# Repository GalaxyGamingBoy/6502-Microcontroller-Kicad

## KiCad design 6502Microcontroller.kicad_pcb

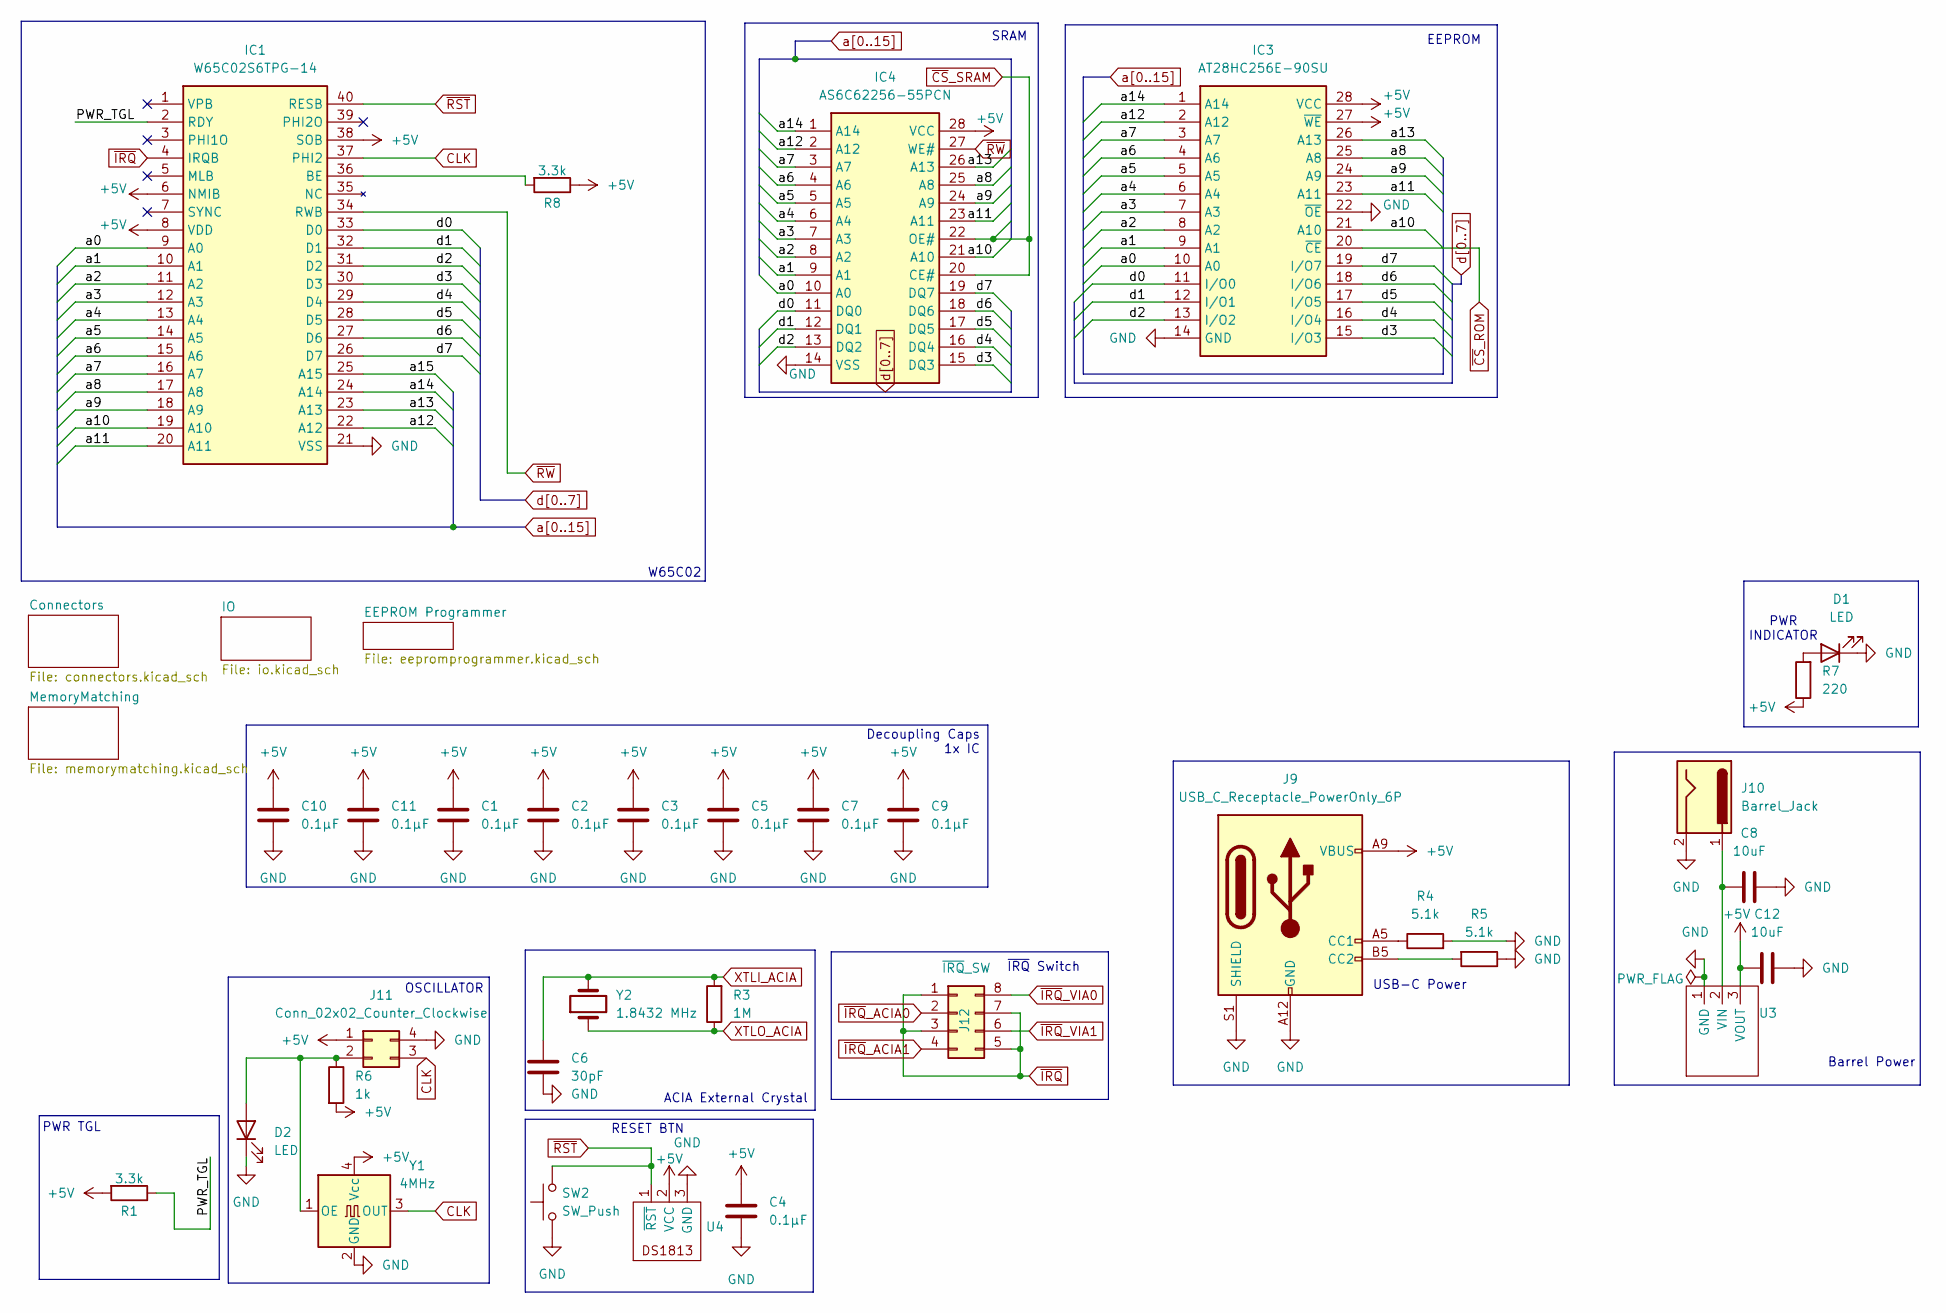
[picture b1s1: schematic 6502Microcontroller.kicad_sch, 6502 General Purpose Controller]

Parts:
C1, C2, C3, C4, C5, C7, C9, C10, C11: 0.1µF; C_0603_1608Metric_Pad1.08x0.95mm_HandSolder
C6: 30pF; C_0603_1608Metric_Pad1.08x0.95mm_HandSolder
C8, C12: 10uF; C_0603_1608Metric_Pad1.08x0.95mm_HandSolder
D1, D2: LED; LED_0603_1608Metric_Pad1.05x0.95mm_HandSolder
IC1: W65C02S6TPG-14; DIP-40_L50.8-W17.8-P2.54-LS15.2-BL; Mouser Part Number 955-W65C02S6TPG-14
IC3: AT28HC256E-90SU; DIP-28_L35.6-W10.2-P2.54-LS7.6-BL-A; Mouser Part Number 556-AT28HC256E90SU
IC4: AS6C62256-55PCN; DIP-28_L35.6-W10.2-P2.54-LS7.6-BL-A; Mouser Part Number 913-AS6C62256-55PCN
J9: USB_C_Receptacle_PowerOnly_6P; USB-C-SMD
J10: Barrel_Jack; BarrelJack_Horizontal
J11: Conn_02x02_Counter_Clockwise; HDR-TH_4P-P2.54-V-F-R2-C2-S2.54
J12: ~{IRQ}_SW; HDR-TH_8P-P2.54-V-M-R2-C4-S2.54
R1, R8: 3.3k; R_0603_1608Metric_Pad0.98x0.95mm_HandSolder
R3: 1M; R_0603_1608Metric_Pad0.98x0.95mm_HandSolder
R4, R5: 5.1k; R_0603_1608Metric_Pad0.98x0.95mm_HandSolder
R6: 1k; R_0603_1608Metric_Pad0.98x0.95mm_HandSolder
R7: 220; R_0603_1608Metric_Pad0.98x0.95mm_HandSolder
SW2: SW_Push; SW-SMD_L3.9-W3.0-P4.45
U3: SOT-89-3_L4.5-W2.5-P1.50-LS4.2-BR
U4: SOT-23-3_L2.9-W1.3-P1.90-LS2.4-BR
Y1: 4MHz; OSC-SMD_4P-L7.0-W5.0-BL-2
Y2: 1.8432 MHz; MP018B

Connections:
+5V: C1.1, C2.1, C3.1, C4.2, C5.1, C7.1, C9.1, C10.1, C11.1, C12.2, IC1.6 (NMIB), IC1.8 (VDD), IC1.38 (SOB), IC3.27 (~WE), IC3.28 (VCC), IC4.28 (VCC), J9.A9 (VBUS), J9.B9 (VBUS), J11.1, R1.2, R6.2, R7.1, R8.1, U3.3 (VOUT), U4.2 (VCC), Y1.4 (Vcc); also elsewhere on the board
/PWR_TGL: IC1.2 (RDY), R1.1
CLK: IC1.37 (PHI2), J11.3, Y1.3 (OUT); also elsewhere on the board
GND: C1.2, C2.2, C3.2, C4.1, C5.2, C6.2, C7.2, C8.2, C9.2, C10.2, C11.2, C12.1, D1.1 (K), D2.1 (K), IC1.21 (VSS), IC3.14 (GND), IC3.22 (~OE), IC4.14 (VSS), J9.A12 (GND), J9.B12 (GND), J9.S1 (SHIELD), J10.2, J11.4, R4.2, R5.1, SW2.1, U3.1 (GND), U4.3 (GND), Y1.2 (GND); also elsewhere on the board
unnamed: D1.2 (A), R7.2
unnamed: D2.2 (A), J11.2, R6.1, Y1.1 (OE)
unnamed: IC1.36 (BE), R8.2
unnamed: J9.A5 (CC1), R4.1
unnamed: J9.B5 (CC2), R5.2
unnamed: C8.1, J10.1, U3.2 (VIN)
XTLI_ACIA: C6.1, R3.2, Y2.2; also elsewhere on the board
XTLO_ACIA: R3.1, Y2.1; also elsewhere on the board
a0: IC1.9 (A0), IC3.10 (A0), IC4.10 (A0); also elsewhere on the board
a1: IC1.10 (A1), IC3.9 (A1), IC4.9 (A1); also elsewhere on the board
a2: IC1.11 (A2), IC3.8 (A2), IC4.8 (A2); also elsewhere on the board
a3: IC1.12 (A3), IC3.7 (A3), IC4.7 (A3); also elsewhere on the board
a4: IC1.13 (A4), IC3.6 (A4), IC4.6 (A4)
a5: IC1.14 (A5), IC3.5 (A5), IC4.5 (A5)
a6: IC1.15 (A6), IC3.4 (A6), IC4.4 (A6)
a7: IC1.16 (A7), IC3.3 (A7), IC4.3 (A7)
a8: IC1.17 (A8), IC3.25 (A8), IC4.25 (A8)
a9: IC1.18 (A9), IC3.24 (A9), IC4.24 (A9)
a10: IC1.19 (A10), IC3.21 (A10), IC4.21 (A10); also elsewhere on the board
a11: IC1.20 (A11), IC3.23 (A11), IC4.23 (A11); also elsewhere on the board
a12: IC1.22 (A12), IC3.2 (A12), IC4.2 (A12); also elsewhere on the board
a13: IC1.23 (A13), IC3.26 (A13), IC4.26 (A13); also elsewhere on the board
a14: IC1.24 (A14), IC3.1 (A14), IC4.1 (A14); also elsewhere on the board
a15: IC1.25 (A15); also elsewhere on the board
d0: IC1.33 (D0), IC3.11 (I/O0), IC4.11 (DQ0); also elsewhere on the board
d1: IC1.32 (D1), IC3.12 (I/O1), IC4.12 (DQ1); also elsewhere on the board
d2: IC1.31 (D2), IC3.13 (I/O2), IC4.13 (DQ2); also elsewhere on the board
d3: IC1.30 (D3), IC3.15 (I/O3), IC4.15 (DQ3); also elsewhere on the board
d4: IC1.29 (D4), IC3.16 (I/O4), IC4.16 (DQ4); also elsewhere on the board
d5: IC1.28 (D5), IC3.17 (I/O5), IC4.17 (DQ5); also elsewhere on the board
d6: IC1.27 (D6), IC3.18 (I/O6), IC4.18 (DQ6); also elsewhere on the board
d7: IC1.26 (D7), IC3.19 (I/O7), IC4.19 (DQ7); also elsewhere on the board
~CS_ROM: IC3.20 (~CE); also elsewhere on the board
~CS_SRAM: IC4.20 (CE#), IC4.22 (OE#); also elsewhere on the board
~IRQ: IC1.4 (IRQB), J12.1, J12.3, J12.5, J12.7
~IRQ_ACIA0: J12.2; also elsewhere on the board
~IRQ_ACIA1: J12.4; also elsewhere on the board
~IRQ_VIA0: J12.8; also elsewhere on the board
~IRQ_VIA1: J12.6; also elsewhere on the board
~RST: IC1.40 (RESB), SW2.2, U4.1 (~RST); also elsewhere on the board
~RW: IC1.34 (RWB), IC4.27 (WE#); also elsewhere on the board

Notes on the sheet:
PWR TGL
EEPROM
RESET BTN
~{IRQ} Switch
PWR INDICATOR
OSCILLATOR
Decoupling Caps 1x IC
ACIA External Crystal
SRAM
W65C02
Barrel Power
USB-C Power

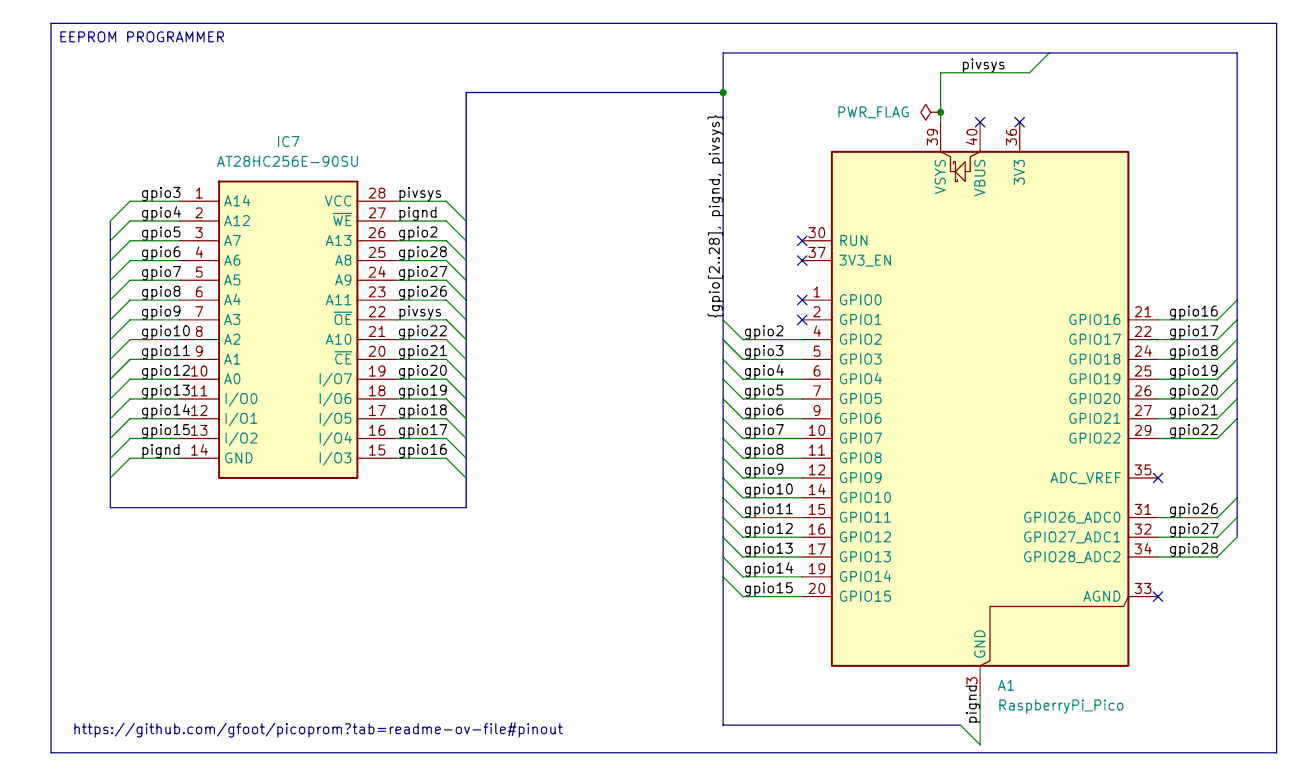
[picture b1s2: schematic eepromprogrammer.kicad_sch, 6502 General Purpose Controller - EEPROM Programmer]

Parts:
A1: RaspberryPi_Pico
IC7: AT28HC256E-90SU; Mouser Part Number 556-AT28HC256E90SU

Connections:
unnamed: A1.4 (GPIO2), IC7.26 (A13)
unnamed: A1.5 (GPIO3), IC7.1 (A14)
unnamed: A1.6 (GPIO4), IC7.2 (A12)
unnamed: A1.7 (GPIO5), IC7.3 (A7)
unnamed: A1.9 (GPIO6), IC7.4 (A6)
unnamed: A1.10 (GPIO7), IC7.5 (A5)
unnamed: A1.11 (GPIO8), IC7.6 (A4)
unnamed: A1.12 (GPIO9), IC7.7 (A3)
unnamed: A1.3 (GND), A1.8 (GND), A1.13 (GND), A1.18 (GND), A1.23 (GND), A1.28 (GND), A1.38 (GND), IC7.14 (GND), IC7.27 (~WE)
unnamed: A1.14 (GPIO10), IC7.8 (A2)
unnamed: A1.15 (GPIO11), IC7.9 (A1)
unnamed: A1.16 (GPIO12), IC7.10 (A0)
unnamed: A1.17 (GPIO13), IC7.11 (I/O0)
unnamed: A1.19 (GPIO14), IC7.12 (I/O1)
unnamed: A1.20 (GPIO15), IC7.13 (I/O2)
unnamed: A1.21 (GPIO16), IC7.15 (I/O3)
unnamed: A1.22 (GPIO17), IC7.16 (I/O4)
unnamed: A1.24 (GPIO18), IC7.17 (I/O5)
unnamed: A1.25 (GPIO19), IC7.18 (I/O6)
unnamed: A1.26 (GPIO20), IC7.19 (I/O7)
unnamed: A1.27 (GPIO21), IC7.20 (~CE)
unnamed: A1.29 (GPIO22), IC7.21 (A10)
unnamed: A1.31 (GPIO26_ADC0), IC7.23 (A11)
unnamed: A1.32 (GPIO27_ADC1), IC7.24 (A9)
unnamed: A1.34 (GPIO28_ADC2), IC7.25 (A8)
unnamed: A1.39 (VSYS), IC7.22 (~OE), IC7.28 (VCC)

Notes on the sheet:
EEPROM PROGRAMMER
https://github.com/gfoot/picoprom?tab=readme-ov-file#pinout

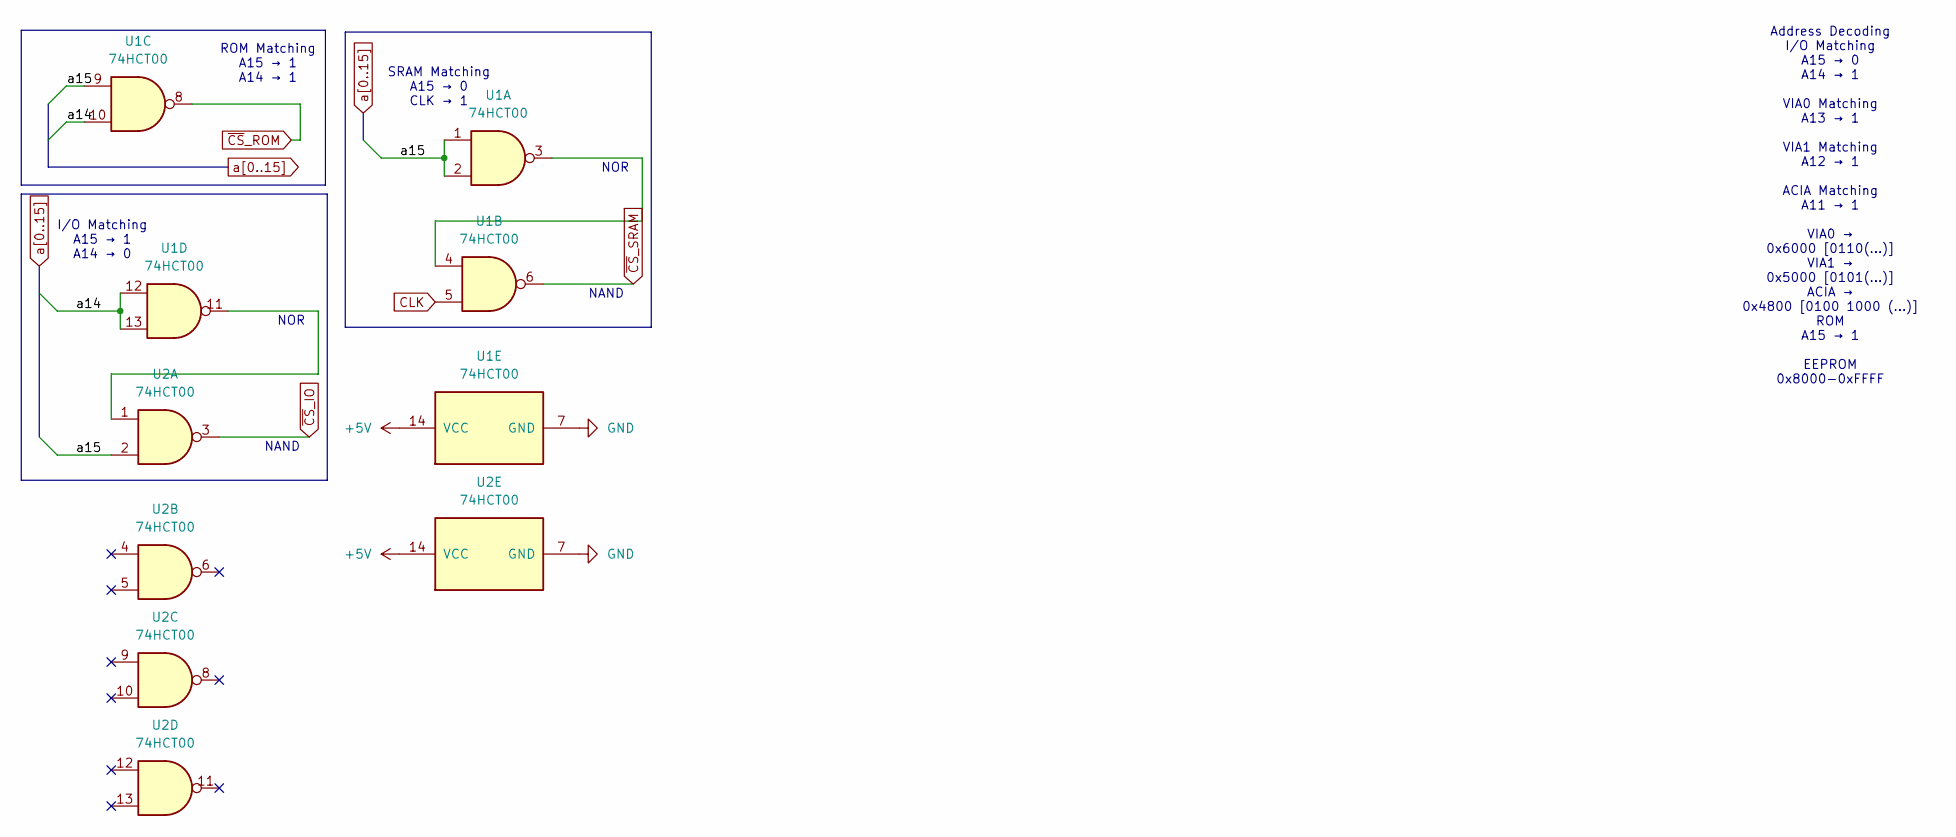
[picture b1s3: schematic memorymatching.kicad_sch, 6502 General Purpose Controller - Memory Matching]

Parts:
U1, U2: 74HCT00; DIP-14_L17.8-W10.2-P2.54-BL

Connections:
+5V: U1.14 (VCC), U2.14 (VCC); also elsewhere on the board
CLK: U1.5; also elsewhere on the board
GND: U1.7 (GND), U2.7 (GND); also elsewhere on the board
unnamed: U1.3, U1.4
unnamed: U1.11, U2.1
a14: U1.10, U1.12, U1.13; also elsewhere on the board
a15: U1.1, U1.2, U1.9, U2.2; also elsewhere on the board
~CS_IO: U2.3; also elsewhere on the board
~CS_ROM: U1.8; also elsewhere on the board
~CS_SRAM: U1.6; also elsewhere on the board

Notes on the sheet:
NOR
Address Decoding I/O Matching A15 → 0 A14 → 1 VIA0 Matching A13 → 1 VIA1 Matching A12 → 1 ACIA Matching A11 → 1 VIA0 → 0x6000 [0110(...)] VIA1 → 0x5000 [0101(...)] ACIA → 0x4800 [0100 1000 (...)] ROM A15 → 1 EEPROM 0x8000-0xFFFF
I/O Matching A15 → 1 A14 → 0
SRAM Matching A15 → 0 CLK → 1
NAND
ROM Matching A15 → 1 A14 → 1

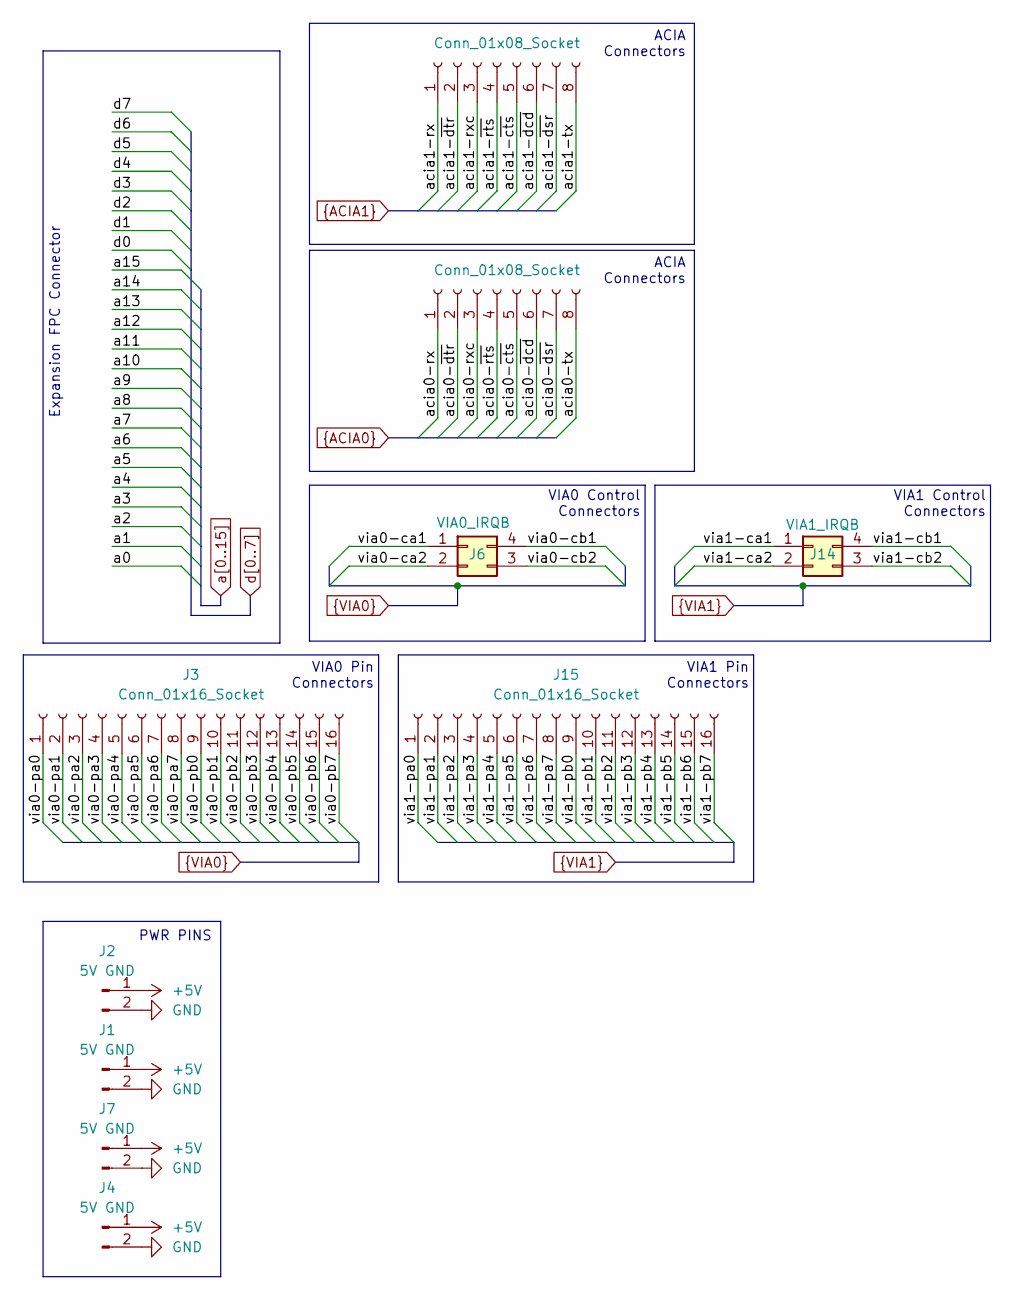
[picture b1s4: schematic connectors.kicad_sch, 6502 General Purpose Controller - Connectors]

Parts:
J1, J2, J4, J7: 5V GND; HDR-TH_2P-P2.54-V-F-1
J3, J15: Conn_01x16_Socket; HDR-TH_16P-P2.54-V-F-4
J5, J8: Conn_01x08_Socket; HDR-TH_8P-P2.54-V-F
J6: VIA0_IRQB; HDR-TH_4P-P2.54-V-F-R2-C2-S2.54
J14: VIA1_IRQB; HDR-TH_4P-P2.54-V-F-R2-C2-S2.54

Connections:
+5V: J1.1, J2.1, J4.1, J7.1; also elsewhere on the board
GND: J1.2, J2.2, J4.2, J7.2; also elsewhere on the board
acia0-rx: J5.1; also elsewhere on the board
acia0-rxc: J5.3; also elsewhere on the board
acia0-tx: J5.8; also elsewhere on the board
acia0-~cts: J5.5; also elsewhere on the board
acia0-~dcd: J5.6; also elsewhere on the board
acia0-~dsr: J5.7; also elsewhere on the board
acia0-~dtr: J5.2; also elsewhere on the board
acia0-~rts: J5.4; also elsewhere on the board
acia1-rx: J8.1; also elsewhere on the board
acia1-rxc: J8.3; also elsewhere on the board
acia1-tx: J8.8; also elsewhere on the board
acia1-~cts: J8.5; also elsewhere on the board
acia1-~dcd: J8.6; also elsewhere on the board
acia1-~dsr: J8.7; also elsewhere on the board
acia1-~dtr: J8.2; also elsewhere on the board
acia1-~rts: J8.4; also elsewhere on the board
via0-ca1: J6.1; also elsewhere on the board
via0-ca2: J6.2; also elsewhere on the board
via0-cb1: J6.4; also elsewhere on the board
via0-cb2: J6.3; also elsewhere on the board
via0-pa0: J3.1; also elsewhere on the board
via0-pa1: J3.2; also elsewhere on the board
via0-pa2: J3.3; also elsewhere on the board
via0-pa3: J3.4; also elsewhere on the board
via0-pa4: J3.5; also elsewhere on the board
via0-pa5: J3.6; also elsewhere on the board
via0-pa6: J3.7; also elsewhere on the board
via0-pa7: J3.8; also elsewhere on the board
via0-pb0: J3.9; also elsewhere on the board
via0-pb1: J3.10; also elsewhere on the board
via0-pb2: J3.11; also elsewhere on the board
via0-pb3: J3.12; also elsewhere on the board
via0-pb4: J3.13; also elsewhere on the board
via0-pb5: J3.14; also elsewhere on the board
via0-pb6: J3.15; also elsewhere on the board
via0-pb7: J3.16; also elsewhere on the board
via1-ca1: J14.1; also elsewhere on the board
via1-ca2: J14.2; also elsewhere on the board
via1-cb1: J14.4; also elsewhere on the board
via1-cb2: J14.3; also elsewhere on the board
via1-pa0: J15.1; also elsewhere on the board
via1-pa1: J15.2; also elsewhere on the board
via1-pa2: J15.3; also elsewhere on the board
via1-pa3: J15.4; also elsewhere on the board
via1-pa4: J15.5; also elsewhere on the board
via1-pa5: J15.6; also elsewhere on the board
via1-pa6: J15.7; also elsewhere on the board
via1-pa7: J15.8; also elsewhere on the board
via1-pb0: J15.9; also elsewhere on the board
via1-pb1: J15.10; also elsewhere on the board
via1-pb2: J15.11; also elsewhere on the board
via1-pb3: J15.12; also elsewhere on the board
via1-pb4: J15.13; also elsewhere on the board
via1-pb5: J15.14; also elsewhere on the board
via1-pb6: J15.15; also elsewhere on the board
via1-pb7: J15.16; also elsewhere on the board

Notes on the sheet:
ACIA Connectors
Expansion FPC Connector
VIA0 Control Connectors
PWR PINS
VIA1 Pin Connectors
VIA1 Control Connectors
VIA0 Pin Connectors

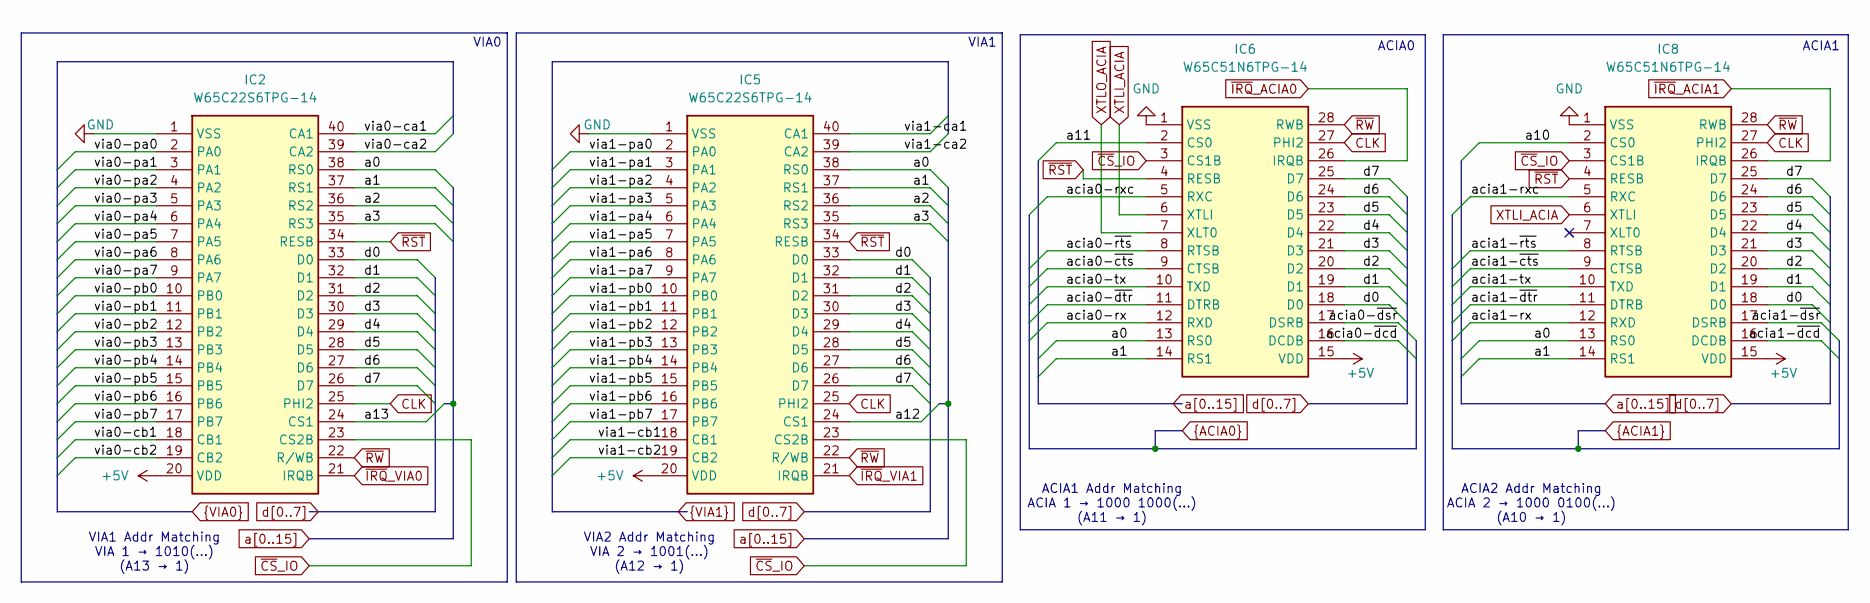
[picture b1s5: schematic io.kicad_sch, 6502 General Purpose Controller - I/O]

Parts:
IC2, IC5: W65C22S6TPG-14; DIP-40_L50.8-W17.8-P2.54-LS15.2-BL; Mouser Part Number 955-W65C22S6TPG-14
IC6, IC8: W65C51N6TPG-14; DIP-28_L35.6-W10.2-P2.54-LS7.6-BL-A; Mouser Part Number 955-W65C51N6TPG-14

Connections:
+5V: IC2.20 (VDD), IC5.20 (VDD), IC6.15 (VDD), IC8.15 (VDD); also elsewhere on the board
CLK: IC2.25 (PHI2), IC5.25 (PHI2), IC6.27 (PHI2), IC8.27 (PHI2); also elsewhere on the board
GND: IC2.1 (VSS), IC5.1 (VSS), IC6.1 (VSS), IC8.1 (VSS); also elsewhere on the board
XTLI_ACIA: IC6.6 (XTLI), IC8.6 (XTLI); also elsewhere on the board
XTLO_ACIA: IC6.7 (XLT0); also elsewhere on the board
a0: IC2.38 (RS0), IC5.38 (RS0), IC6.13 (RS0), IC8.13 (RS0); also elsewhere on the board
a1: IC2.37 (RS1), IC5.37 (RS1), IC6.14 (RS1), IC8.14 (RS1); also elsewhere on the board
a2: IC2.36 (RS2), IC5.36 (RS2); also elsewhere on the board
a3: IC2.35 (RS3), IC5.35 (RS3); also elsewhere on the board
a10: IC8.2 (CS0); also elsewhere on the board
a11: IC6.2 (CS0); also elsewhere on the board
a12: IC5.24 (CS1); also elsewhere on the board
a13: IC2.24 (CS1); also elsewhere on the board
acia0-rx: IC6.12 (RXD); also elsewhere on the board
acia0-rxc: IC6.5 (RXC); also elsewhere on the board
acia0-tx: IC6.10 (TXD); also elsewhere on the board
acia0-~cts: IC6.9 (CTSB); also elsewhere on the board
acia0-~dcd: IC6.16 (DCDB); also elsewhere on the board
acia0-~dsr: IC6.17 (DSRB); also elsewhere on the board
acia0-~dtr: IC6.11 (DTRB); also elsewhere on the board
acia0-~rts: IC6.8 (RTSB); also elsewhere on the board
acia1-rx: IC8.12 (RXD); also elsewhere on the board
acia1-rxc: IC8.5 (RXC); also elsewhere on the board
acia1-tx: IC8.10 (TXD); also elsewhere on the board
acia1-~cts: IC8.9 (CTSB); also elsewhere on the board
acia1-~dcd: IC8.16 (DCDB); also elsewhere on the board
acia1-~dsr: IC8.17 (DSRB); also elsewhere on the board
acia1-~dtr: IC8.11 (DTRB); also elsewhere on the board
acia1-~rts: IC8.8 (RTSB); also elsewhere on the board
d0: IC2.33 (D0), IC5.33 (D0), IC6.18 (D0), IC8.18 (D0); also elsewhere on the board
d1: IC2.32 (D1), IC5.32 (D1), IC6.19 (D1), IC8.19 (D1); also elsewhere on the board
d2: IC2.31 (D2), IC5.31 (D2), IC6.20 (D2), IC8.20 (D2); also elsewhere on the board
d3: IC2.30 (D3), IC5.30 (D3), IC6.21 (D3), IC8.21 (D3); also elsewhere on the board
d4: IC2.29 (D4), IC5.29 (D4), IC6.22 (D4), IC8.22 (D4); also elsewhere on the board
d5: IC2.28 (D5), IC5.28 (D5), IC6.23 (D5), IC8.23 (D5); also elsewhere on the board
d6: IC2.27 (D6), IC5.27 (D6), IC6.24 (D6), IC8.24 (D6); also elsewhere on the board
d7: IC2.26 (D7), IC5.26 (D7), IC6.25 (D7), IC8.25 (D7); also elsewhere on the board
via0-ca1: IC2.40 (CA1); also elsewhere on the board
via0-ca2: IC2.39 (CA2); also elsewhere on the board
via0-cb1: IC2.18 (CB1); also elsewhere on the board
via0-cb2: IC2.19 (CB2); also elsewhere on the board
via0-pa0: IC2.2 (PA0); also elsewhere on the board
via0-pa1: IC2.3 (PA1); also elsewhere on the board
via0-pa2: IC2.4 (PA2); also elsewhere on the board
via0-pa3: IC2.5 (PA3); also elsewhere on the board
via0-pa4: IC2.6 (PA4); also elsewhere on the board
via0-pa5: IC2.7 (PA5); also elsewhere on the board
via0-pa6: IC2.8 (PA6); also elsewhere on the board
via0-pa7: IC2.9 (PA7); also elsewhere on the board
via0-pb0: IC2.10 (PB0); also elsewhere on the board
via0-pb1: IC2.11 (PB1); also elsewhere on the board
via0-pb2: IC2.12 (PB2); also elsewhere on the board
via0-pb3: IC2.13 (PB3); also elsewhere on the board
via0-pb4: IC2.14 (PB4); also elsewhere on the board
via0-pb5: IC2.15 (PB5); also elsewhere on the board
via0-pb6: IC2.16 (PB6); also elsewhere on the board
via0-pb7: IC2.17 (PB7); also elsewhere on the board
via1-ca1: IC5.40 (CA1); also elsewhere on the board
via1-ca2: IC5.39 (CA2); also elsewhere on the board
via1-cb1: IC5.18 (CB1); also elsewhere on the board
via1-cb2: IC5.19 (CB2); also elsewhere on the board
via1-pa0: IC5.2 (PA0); also elsewhere on the board
via1-pa1: IC5.3 (PA1); also elsewhere on the board
via1-pa2: IC5.4 (PA2); also elsewhere on the board
via1-pa3: IC5.5 (PA3); also elsewhere on the board
via1-pa4: IC5.6 (PA4); also elsewhere on the board
via1-pa5: IC5.7 (PA5); also elsewhere on the board
via1-pa6: IC5.8 (PA6); also elsewhere on the board
via1-pa7: IC5.9 (PA7); also elsewhere on the board
via1-pb0: IC5.10 (PB0); also elsewhere on the board
via1-pb1: IC5.11 (PB1); also elsewhere on the board
via1-pb2: IC5.12 (PB2); also elsewhere on the board
via1-pb3: IC5.13 (PB3); also elsewhere on the board
via1-pb4: IC5.14 (PB4); also elsewhere on the board
via1-pb5: IC5.15 (PB5); also elsewhere on the board
via1-pb6: IC5.16 (PB6); also elsewhere on the board
via1-pb7: IC5.17 (PB7); also elsewhere on the board
~CS_IO: IC2.23 (CS2B), IC5.23 (CS2B), IC6.3 (CS1B), IC8.3 (CS1B); also elsewhere on the board
~IRQ_ACIA0: IC6.26 (IRQB); also elsewhere on the board
~IRQ_ACIA1: IC8.26 (IRQB); also elsewhere on the board
~IRQ_VIA0: IC2.21 (IRQB); also elsewhere on the board
~IRQ_VIA1: IC5.21 (IRQB); also elsewhere on the board
~RST: IC2.34 (RESB), IC5.34 (RESB), IC6.4 (RESB), IC8.4 (RESB); also elsewhere on the board
~RW: IC2.22 (R/WB), IC5.22 (R/WB), IC6.28 (RWB), IC8.28 (RWB); also elsewhere on the board

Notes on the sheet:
VIA1
ACIA2 Addr Matching ACIA 2 → 1000 0100(...) (A10 → 1)
VIA0
ACIA0
VIA1 Addr Matching VIA 1 → 1010(...) (A13 → 1)
ACIA1 Addr Matching ACIA 1 → 1000 1000(...) (A11 → 1)
VIA2 Addr Matching VIA 2 → 1001(...) (A12 → 1)
ACIA1

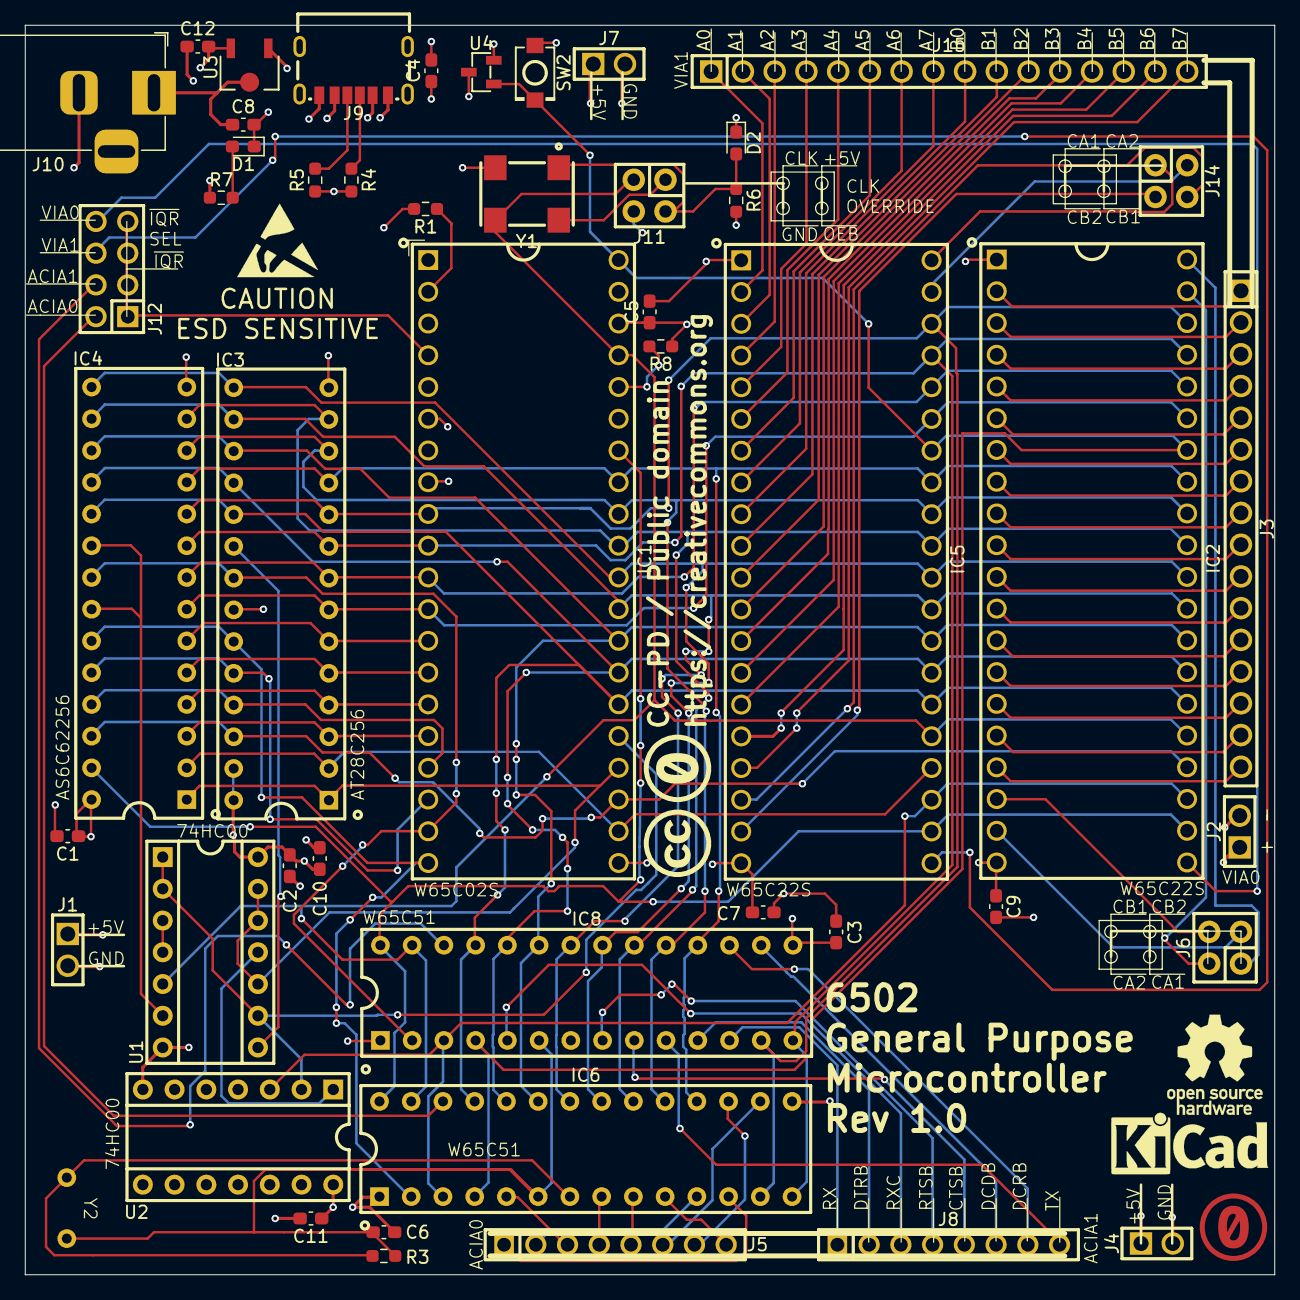
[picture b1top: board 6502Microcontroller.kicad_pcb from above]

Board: 4 copper layers, 100.0 x 100.0 mm, 49 parts (0 on the bottom side), 104 nets.

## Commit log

2025-05-28 feat: add lcsc footprints
2025-05-28 feat: init rev 1
2025-05-30 add reset supervisor ic
2025-06-05 feat: add proper headers

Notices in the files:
parts and their libraries:
CC-PD / Public domain
